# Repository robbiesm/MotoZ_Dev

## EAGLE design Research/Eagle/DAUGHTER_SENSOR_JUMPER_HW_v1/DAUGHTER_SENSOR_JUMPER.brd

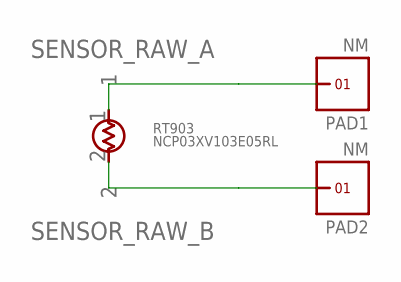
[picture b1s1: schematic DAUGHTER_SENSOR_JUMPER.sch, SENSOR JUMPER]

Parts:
PAD1, PAD2: NM; PAD_2X3
RT903: NCP03XV103E05RL; 0201

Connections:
SENSOR_RAW_A: PAD1.1, RT903.1
SENSOR_RAW_B: PAD2.1, RT903.2

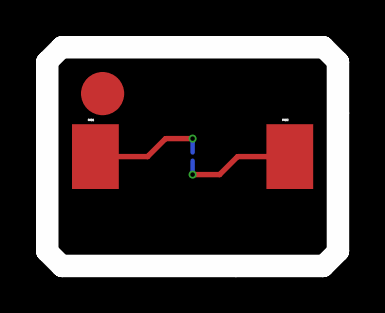
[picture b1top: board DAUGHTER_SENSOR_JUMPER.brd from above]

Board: 2 copper layers, 16.2 x 12.2 mm, 3 parts (1 on the bottom side), 2 nets.

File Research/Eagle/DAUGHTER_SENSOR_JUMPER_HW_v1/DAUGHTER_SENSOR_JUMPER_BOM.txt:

Partlist exported at 7/24/2016 6:41 PM

Qty Value           Device     Package Parts      Description                  MPN                                  SUPPLIER  
1   NCP03XV103E05RL THERMISTOR 0201    RT903      Thmistor, NTC 10Khm 3%, 0201 NCP03XV103XV103E05RL/NTCG0603UH103HT MURARA/TDK
2   NM              PUCK       PAD_2X3 PAD1, PAD2 test pad

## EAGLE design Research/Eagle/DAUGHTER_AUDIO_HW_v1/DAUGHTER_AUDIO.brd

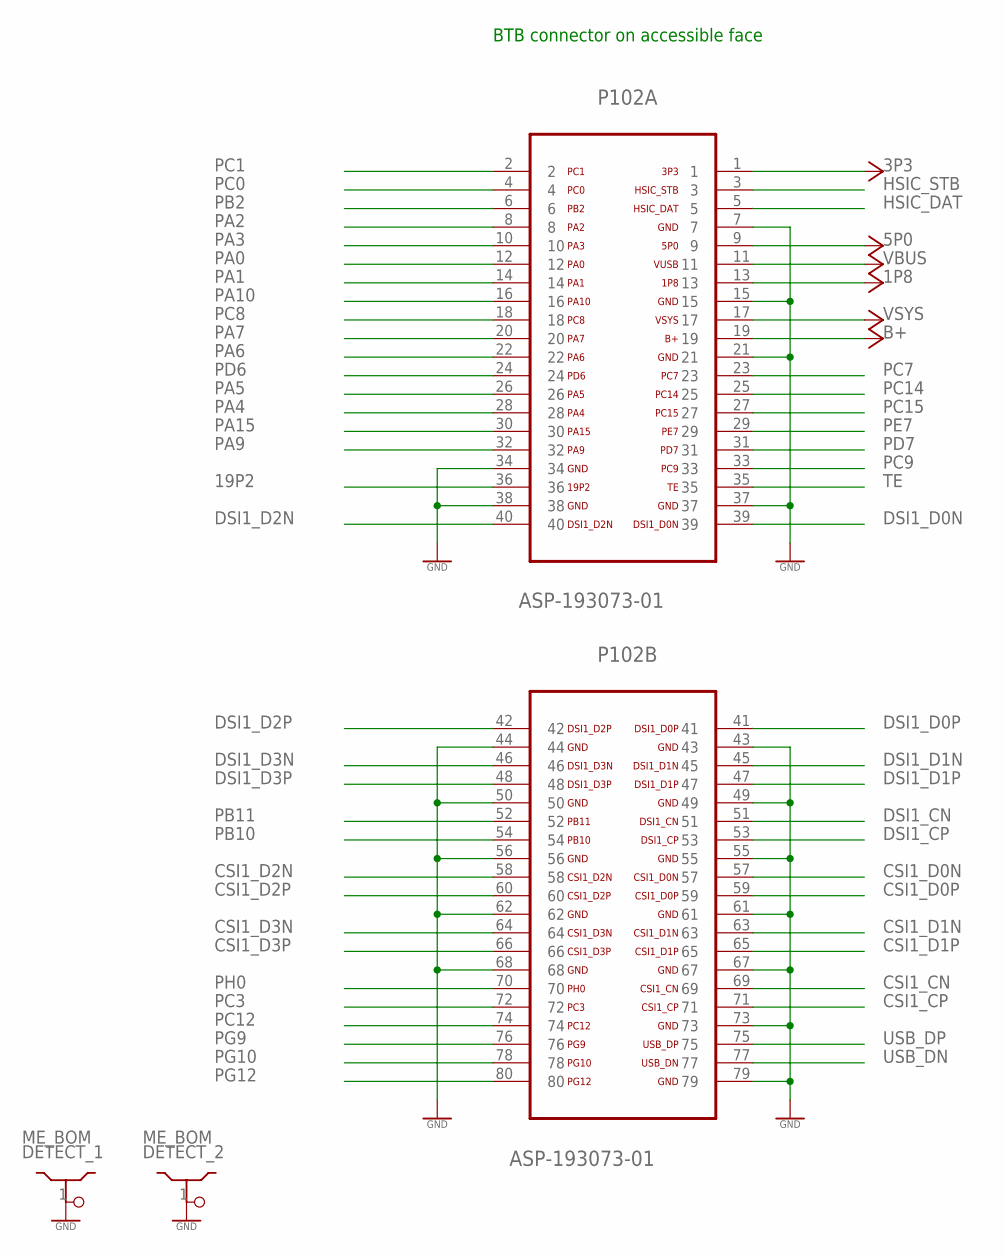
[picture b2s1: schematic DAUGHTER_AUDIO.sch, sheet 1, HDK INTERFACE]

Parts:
DETECT_1, DETECT_2: ME_BOM; PLUG
P102: ASP-193073-01; FTMH-140-02-L-DV-ES-P-TR; MPN ASP-193073-01

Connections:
1P8: P102.13; also elsewhere on the board
3P3: P102.1; also elsewhere on the board
5P0: P102.9
19P2: P102.36
B+: P102.19; also elsewhere on the board
CSI1_CN: P102.69
CSI1_CP: P102.71
CSI1_D0N: P102.57
CSI1_D0P: P102.59
CSI1_D1N: P102.63
CSI1_D1P: P102.65
CSI1_D2N: P102.58
CSI1_D2P: P102.60
CSI1_D3N: P102.64
CSI1_D3P: P102.66
DSI1_CN: P102.51
DSI1_CP: P102.53
DSI1_D0N: P102.39
DSI1_D0P: P102.41
DSI1_D1N: P102.45
DSI1_D1P: P102.47
DSI1_D2N: P102.40
DSI1_D2P: P102.42
DSI1_D3N: P102.46
DSI1_D3P: P102.48
GND: DETECT_1.1, DETECT_2.1, P102.7, P102.15, P102.21, P102.34, P102.37, P102.38, P102.43, P102.44, P102.49, P102.50, P102.55, P102.56, P102.61, P102.62, P102.67, P102.68, P102.73, P102.79; also elsewhere on the board
HSIC_DAT: P102.5
HSIC_STB: P102.3
PA0: P102.12
PA1: P102.14
PA2: P102.8
PA3: P102.10
PA4: P102.28
PA5: P102.26
PA6: P102.22
PA7: P102.20
PA9: P102.32
PA10: P102.16
PA15: P102.30
PB2: P102.6
PB10: P102.54; also elsewhere on the board
PB11: P102.52; also elsewhere on the board
PC0: P102.4; also elsewhere on the board
PC1: P102.2; also elsewhere on the board
PC3: P102.72
PC7: P102.23; also elsewhere on the board
PC8: P102.18
PC9: P102.33
PC12: P102.74
PC14: P102.25; also elsewhere on the board
PC15: P102.27; also elsewhere on the board
PD6: P102.24
PD7: P102.31; also elsewhere on the board
PE7: P102.29; also elsewhere on the board
PG9: P102.76; also elsewhere on the board
PG10: P102.78; also elsewhere on the board
PG12: P102.80
PH0: P102.70; also elsewhere on the board
TE: P102.35
USB_DN: P102.77
USB_DP: P102.75
VBUS: P102.11
VSYS: P102.17

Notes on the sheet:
BTB connector on accessible face

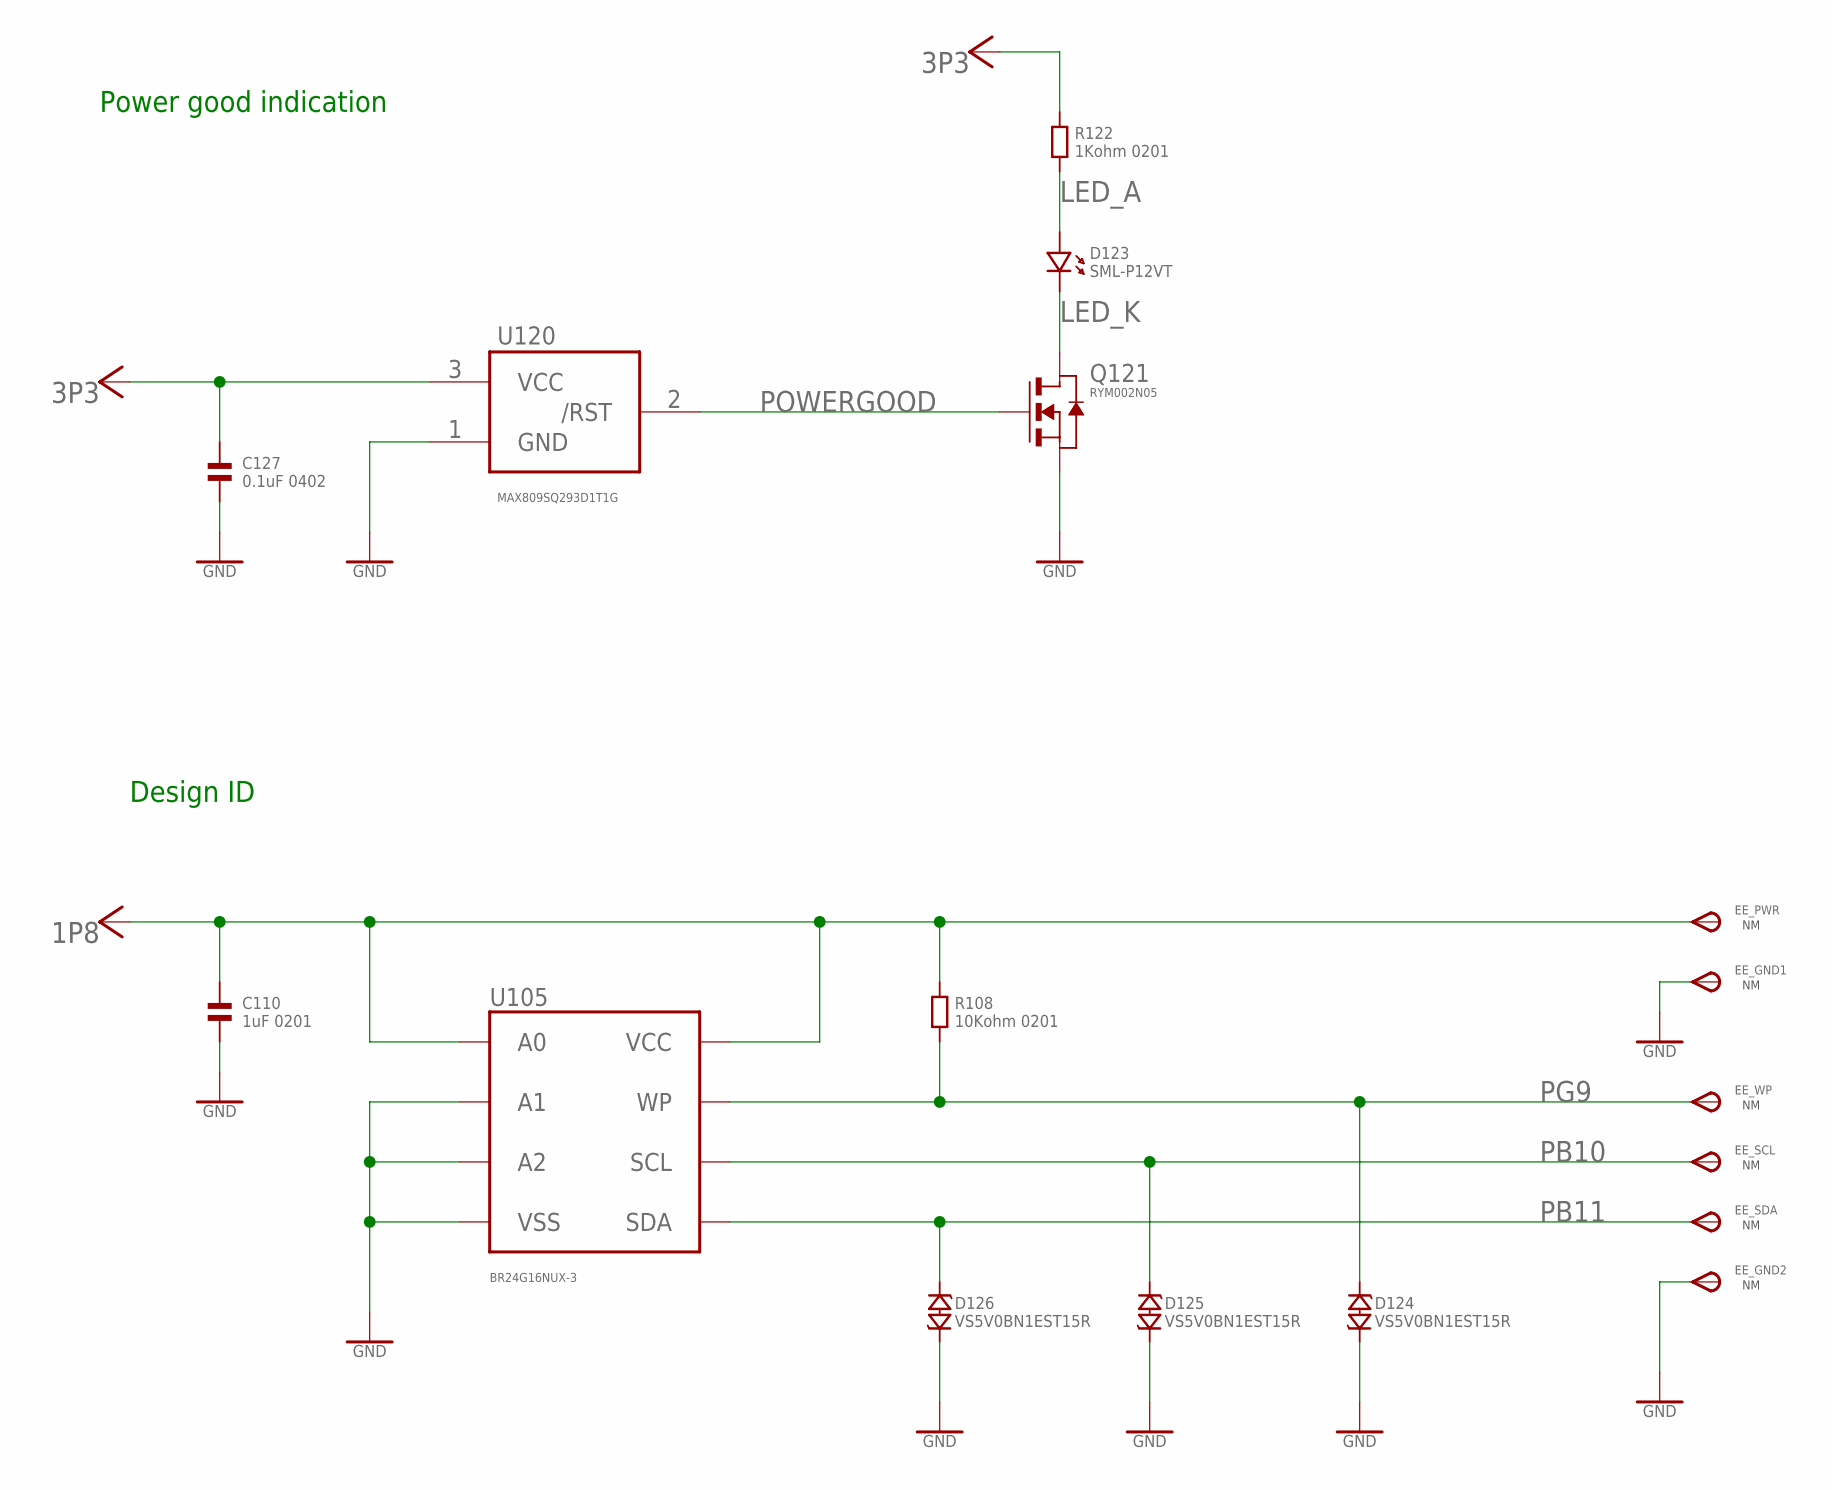
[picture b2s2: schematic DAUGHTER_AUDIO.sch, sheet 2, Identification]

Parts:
C110: 1uF 0201; 0201
C127: 0.1uF 0402; 0402
D123: SML-P12VT; 0503.LED
D124, D125, D126: VS5V0BN1EST15R; CHIP_0201
EE_GND1, EE_GND2: NM; TP11R
EE_PWR: NM; TP11R
EE_SCL: NM; TP11R
EE_SDA: NM; TP11R
EE_WP: NM; TP11R
Q121: RYM002N05; VMT3
R108: 10Kohm 0201; 0201
R122: 1Kohm 0201; 0201
U105: BR24G16NUX-3; DFN-8
U120: MAX809SQ293D1T1G; SC70-3L

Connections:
1P8: C110.1, EE_PWR.TP, R108.1, U105.P$1 (A0), U105.P$8 (VCC); also elsewhere on the board
3P3: C127.1, R122.1, U120.3 (VCC); also elsewhere on the board
GND: C110.2, C127.2, D124.P$2 (2), D125.P$2 (2), D126.P$2 (2), EE_GND1.TP, EE_GND2.TP, Q121.2 (S), U105.P$2 (A1), U105.P$3 (A2), U105.P$4 (VSS), U105.P$9 (VSS), U120.1 (GND); also elsewhere on the board
LED_A: D123.P$1 (1), R122.2
LED_K: D123.P$2 (2), Q121.3 (D)
PB10: D125.P$1 (1), EE_SCL.TP, U105.P$6 (SCL); also elsewhere on the board
PB11: D126.P$1 (1), EE_SDA.TP, U105.P$5 (SDA); also elsewhere on the board
PG9: D124.P$1 (1), EE_WP.TP, R108.2, U105.P$7 (WP); also elsewhere on the board
POWERGOOD: Q121.1 (G), U120.2 (/RST)

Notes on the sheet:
Power good indication
Design ID

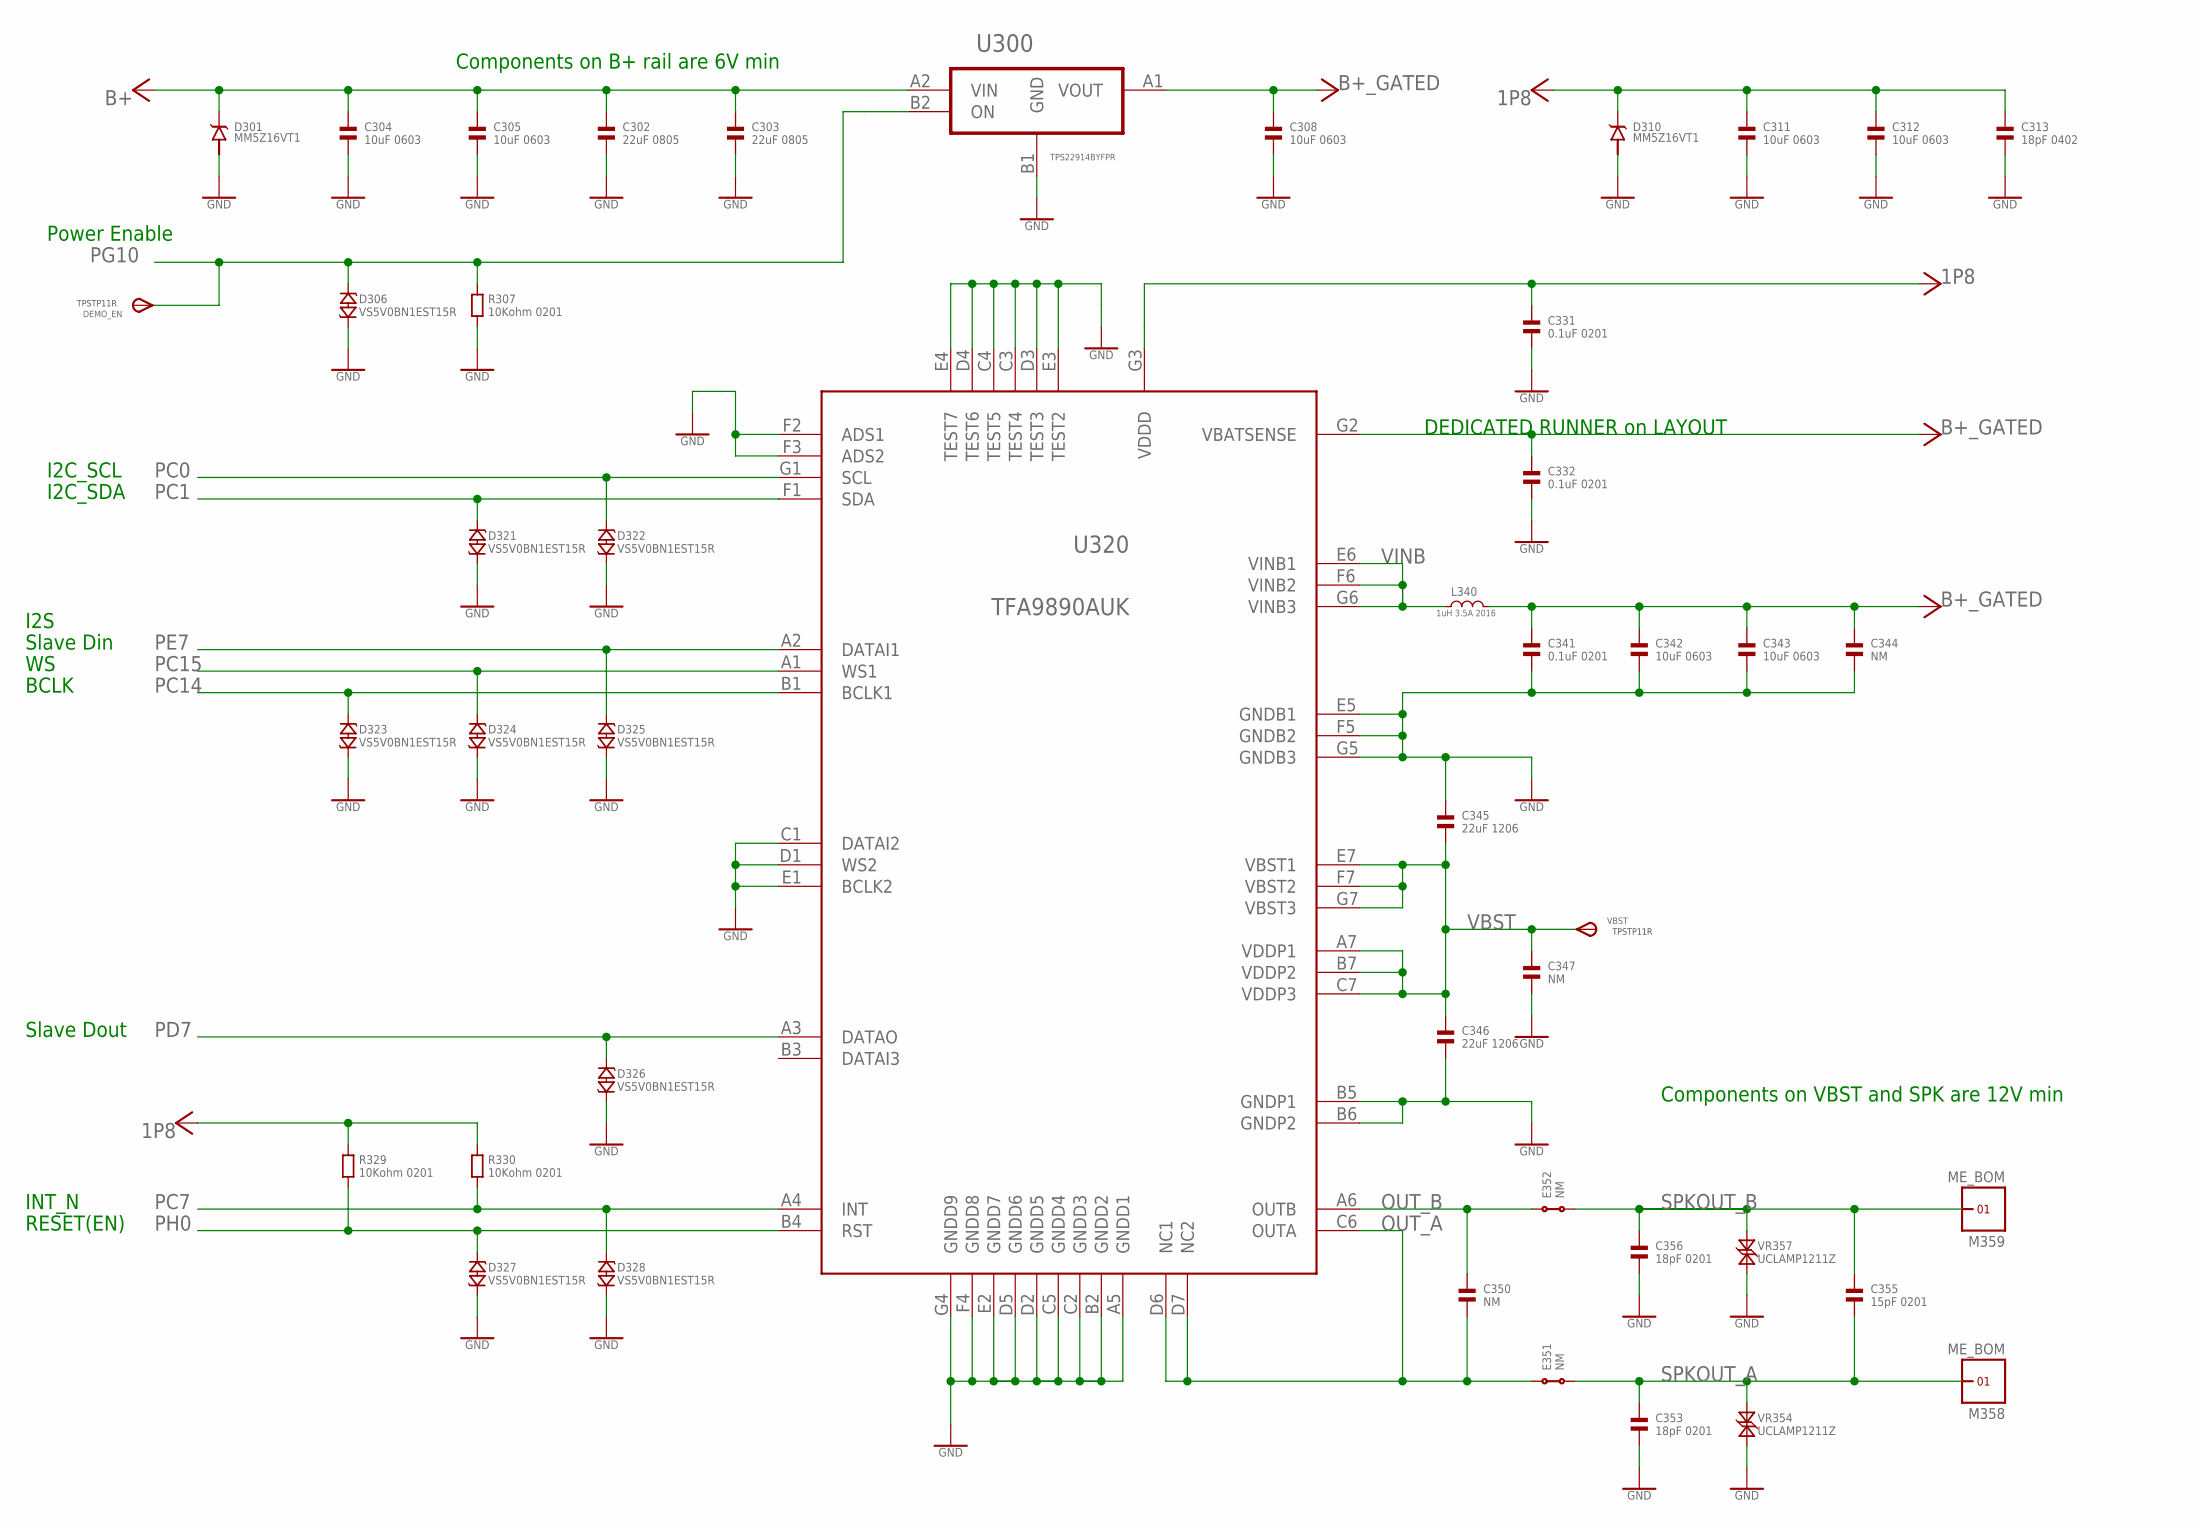
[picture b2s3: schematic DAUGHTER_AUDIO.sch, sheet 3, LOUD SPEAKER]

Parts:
C302, C303: 22uF 0805; 0805
C304, C305, C308, C311, C312, C342, C343: 10uF 0603; 0603
C313: 18pF 0402; 0402
C331, C332, C341: 0.1uF 0201; 0201
C344, C347: NM; 0402
C345, C346: 22uF 1206; 1206
C350: NM; 0201
C353, C356: 18pF 0201; 0201
C355: 15pF 0201; 0201
D301, D310: MM5Z16VT1; SOD523
D306, D321, D322, D323, D324, D325, D326, D327, D328: VS5V0BN1EST15R; CHIP_0201
DEMO_EN: TPSTP11R; TP11R
E351, E352: NM; 0603_SHORT
L340: 1uH 3.5A 2016; 2016
M358, M359: ME_BOM; PUCK
R307, R329, R330: 10Kohm 0201; 0201
U300: TPS22914BYFPR; BGA0_75SQ_PS0_4_P4
U320: TFA9890AUK; BGA7X7
VBST: TPSTP11R; TP11R
VR354, VR357: UCLAMP1211Z; CHIP_0201

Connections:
1P8: C311.1, C312.1, C313.1, C331.1, D310.1, R329.1, R330.1, U320.G3 (VDDD); also elsewhere on the board
B+: C302.1, C303.1, C304.1, C305.1, D301.1, U300.A2 (VIN); also elsewhere on the board
B+_GATED: C308.1, C332.1, C341.1, C342.1, C343.1, C344.1, L340.2, U300.A1 (VOUT), U320.G2 (VBATSENSE)
GND: C302.2, C303.2, C304.2, C305.2, C308.2, C311.2, C312.2, C313.2, C331.2, C332.2, C341.2, C342.2, C343.2, C344.2, C345.1, C346.2, C347.2, C353.2, C356.2, D301.2, D306.P$2 (2), D310.2, D321.P$2 (2), D322.P$2 (2), D323.P$2 (2), D324.P$2 (2), D325.P$2 (2), D326.P$2 (2), D327.P$2 (2), D328.P$2 (2), R307.2, U300.B1 (GND), U320.A5 (GNDD1), U320.B2 (GNDD2), U320.B5 (GNDP1), U320.B6 (GNDP2), U320.C1 (DATAI2), U320.C2 (GNDD3), U320.C3 (TEST4), U320.C4 (TEST5), U320.C5 (GNDD4), U320.D1 (WS2), U320.D2 (GNDD5), U320.D3 (TEST3), U320.D4 (TEST6), U320.D5 (GNDD6), U320.E1 (BCLK2), U320.E2 (GNDD7), U320.E3 (TEST2), U320.E4 (TEST7), U320.E5 (GNDB1), U320.F2 (ADS1), U320.F3 (ADS2), U320.F4 (GNDD8), U320.F5 (GNDB2), U320.G4 (GNDD9), U320.G5 (GNDB3), VR354.P$2 (2), VR357.P$2 (2); also elsewhere on the board
OUT_A: C350.2, E351.1, U320.C6 (OUTA), U320.D6 (NC1), U320.D7 (NC2)
OUT_B: C350.1, E352.1, U320.A6 (OUTB)
PC0: D322.P$1 (1), U320.G1 (SCL); also elsewhere on the board
PC1: D321.P$1 (1), U320.F1 (SDA); also elsewhere on the board
PC7: D328.P$1 (1), R330.2, U320.A4 (INT); also elsewhere on the board
PC14: D323.P$1 (1), U320.B1 (BCLK1); also elsewhere on the board
PC15: D324.P$1 (1), U320.A1 (WS1); also elsewhere on the board
PD7: D326.P$1 (1), U320.A3 (DATAO); also elsewhere on the board
PE7: D325.P$1 (1), U320.A2 (DATAI1); also elsewhere on the board
PG10: D306.P$1 (1), DEMO_EN.TP, R307.1, U300.B2 (ON); also elsewhere on the board
PH0: D327.P$1 (1), R329.2, U320.B4 (RST); also elsewhere on the board
SPKOUT_A: C353.1, C355.2, E351.2, M358.1, VR354.P$1 (1)
SPKOUT_B: C355.1, C356.1, E352.2, M359.1, VR357.P$1 (1)
VBST: C345.2, C346.1, C347.1, U320.A7 (VDDP1), U320.B7 (VDDP2), U320.C7 (VDDP3), U320.E7 (VBST1), U320.F7 (VBST2), U320.G7 (VBST3), VBST.TP
VINB: L340.1, U320.E6 (VINB1), U320.F6 (VINB2), U320.G6 (VINB3)

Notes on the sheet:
Power Enable
I2C_SCL
I2C_SDA
BCLK
I2S
Slave Dout
Slave Din
INT_N
RESET(EN)
DEDICATED RUNNER on LAYOUT
Components on VBST and SPK are 12V min
Components on B+ rail are 6V min

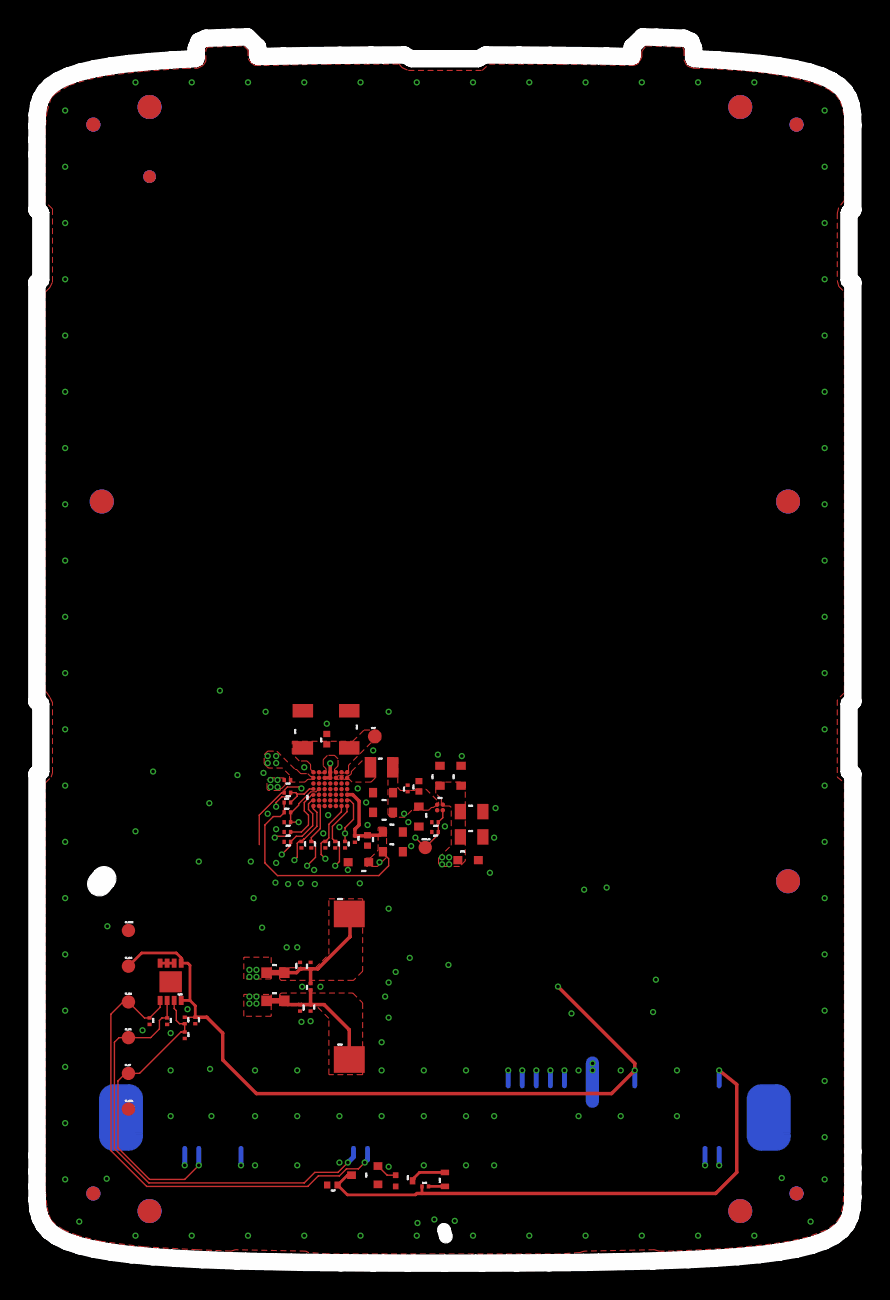
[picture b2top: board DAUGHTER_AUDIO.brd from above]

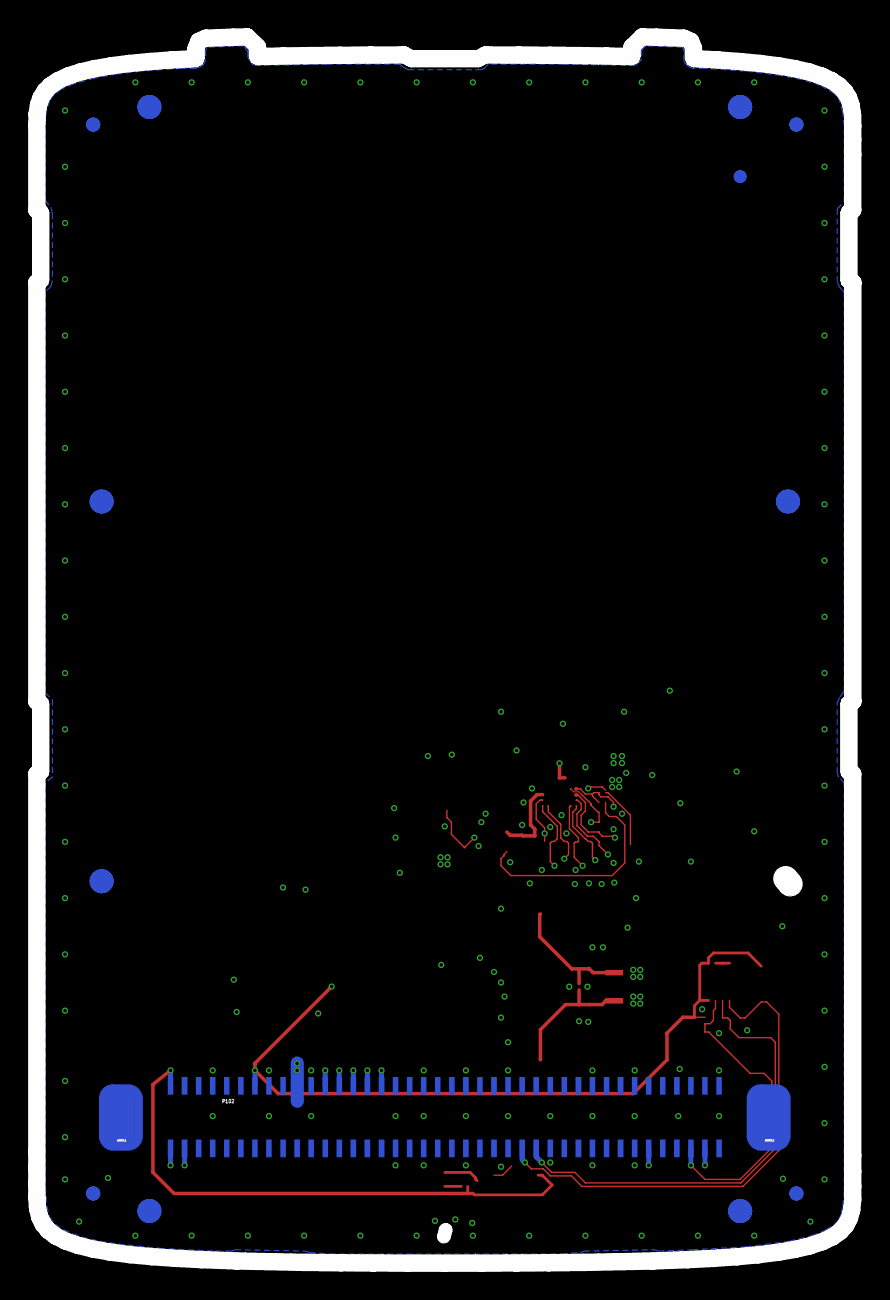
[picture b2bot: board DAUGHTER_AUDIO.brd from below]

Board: 4 copper layers, 58.1 x 87.2 mm, 66 parts (3 on the bottom side), 26 nets.

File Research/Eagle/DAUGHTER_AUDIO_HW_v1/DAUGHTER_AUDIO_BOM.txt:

Partlist exported at 7/24/2016 6:28 PM

Qty Value            Device                   Package                  Parts                                                                  Description                             MPN             SUPPLIER       
3   0.1uF 0201       CAPACITOR.0201           0201                     C331, C332, C341                                                       Ceramic Capacitor, Generic                                             
1   0.1uF 0402       CAPACITOR.0402           0402                     C127                                                                   Ceramic Capacitor, Generic                                             
4   10Kohm 0201      RESISTOR.0201            0201                     R108, R307, R329, R330                                                 Resistor - Generic                                                     
7   10uF 0603        CAPACITOR.0603           0603                     C304, C305, C308, C311, C312, C342, C343                               Ceramic Capacitor, Generic                                             
1   15pF 0201        CAPACITOR.0201           0201                     C355                                                                   Ceramic Capacitor, Generic                                             
2   18pF 0201        CAPACITOR.0201           0201                     C353, C356                                                             Ceramic Capacitor, Generic                                             
1   18pF 0402        CAPACITOR.0402           0402                     C313                                                                   Ceramic Capacitor, Generic                                             
1   1Kohm 0201       RESISTOR.0201            0201                     R122                                                                   Resistor - Generic                                                     
1   1uF 0201         CAPACITOR.0201           0201                     C110                                                                   Ceramic Capacitor, Generic                                             
1   1uH 3.5A 2016    POWER-INDUCTOR.2016      2016                     L340                                                                   Inductor, Power                                                        
2   22uF 0805        CAPACITOR.0805           0805                     C302, C303                                                             Ceramic Capacitor, Generic                                             
2   22uF 1206        CAPACITOR.1206           1206                     C345, C346                                                             Ceramic Capacitor, Generic                                             
1   ASP-193073-01    FTMH-140-02-L-DV-ES-P-TR FTMH-140-02-L-DV-ES-P-TR P102                                                                   MICRO SOCKET, 1.0MM, SMD, 2X40WAY, MALE ASP-193073-01   SAMTEC         
1   BR24G16NUX-3     EEPROMDFN8               DFN-8                    U105                                                                   I2C EE PROM, 8 pin                      BR24G16NUX-3    ROHM           
1   MAX809SQ293D1T1G MAX809                   SC70-3L                  U120                                                                   3-Pin Microprocessor Reset Circuit      MAX809SQ293D1T1 ON-SEMI        
2   ME_BOM           PUCK.PUCK                PUCK                     M358, M359                                                             test pad                                refer to ME BOM refer to ME BOM
2   ME_BOM           SHIELDDETECT             PLUG                     DETECT_1, DETECT_2                                                     Shield, Custom                          refer to ME BOM ref to ME BOM  
2   MM5Z16VT1        DIODE.SOD523             SOD523                   D301, D310                                                             DIODE GENERIC, single, 2 pin            MM5Z16VT1       ON_SEMI        
1   NM               CAPACITOR.0201           0201                     C350                                                                   Ceramic Capacitor, Generic                                             
2   NM               CAPACITOR.0402           0402                     C344, C347                                                             Ceramic Capacitor, Generic                                             
2   NM               SHORT_BAR.0603           0603_SHORT               E351, E352                                                             SHORT BAR - layout feature                                             
6   NM               TPSTP11R                 TP11R                    EE_GND1, EE_GND2, EE_PWR, EE_SCL, EE_SDA, EE_WP                        TEST Point, 1mm diameter, gold                                         
1   RYM002N05        FET-NRYM002N05           VMT3                     Q121                                                                   Generic NMOS FET                        RYM002N05       ROHM           
1   SML-P12VT        LED.0503                 0503.LED                 D123                                                                   LED GENERIC, single, 2 pin              SML-P12VT       ROHM           
1   TFA9890AUK       TFA9890AUK               BGA7X7                   U320                                                                   Audio Power amplifier                   TFA9890AUK      NXP            
1   TPS22914BYFPR    TPS22914BYFPR            BGA0_75SQ_PS0_4_P4       U300                                                                   5V load switch                          TPS22914BYFPR   TI             
2   TPSTP11R         TPSTP11R                 TP11R                    DEMO_EN, VBST                                                          TEST Point, 1mm diameter, gold                                         
2   UCLAMP1211Z      ESD_TVS.0201             CHIP_0201                VR354, VR357                                                           GENERIC TVS,single, 2 pin               UCLAMP1211Z     SEMTECH        
12  VS5V0BN1EST15R   ESD_VARISTOR.0201        CHIP_0201                D124, D125, D126, D306, D321, D322, D323, D324, D325, D326, D327, D328 GENERIC varistor,single, 2 pin          VS5V0BN1EST15R  ROHM

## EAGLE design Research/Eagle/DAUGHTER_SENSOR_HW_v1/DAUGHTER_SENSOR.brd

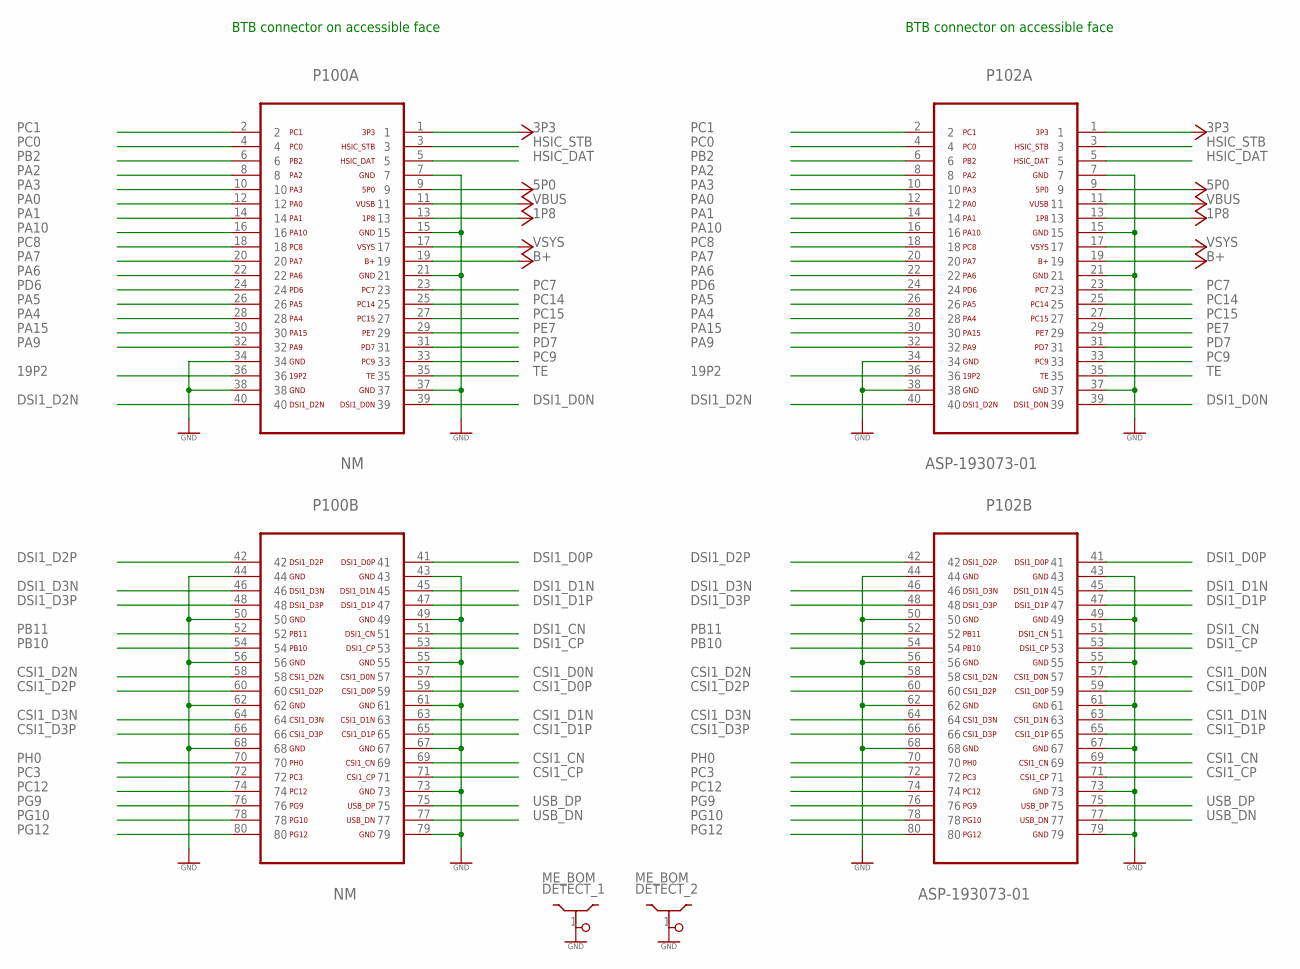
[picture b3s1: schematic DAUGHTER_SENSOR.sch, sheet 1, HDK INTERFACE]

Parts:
DETECT_1, DETECT_2: ME_BOM; PLUG
P100: NM; CLM-140-02-L-D-K_GOLD
P102: ASP-193073-01; FTMH-140-02-L-DV-ES-P-TR; MPN ASP-193073-01

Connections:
1P8: P100.13, P102.13; also elsewhere on the board
3P3: P100.1, P102.1; also elsewhere on the board
5P0: P100.9, P102.9
19P2: P100.36, P102.36
B+: P100.19, P102.19
CSI1_CN: P100.69, P102.69
CSI1_CP: P100.71, P102.71
CSI1_D0N: P100.57, P102.57
CSI1_D0P: P100.59, P102.59
CSI1_D1N: P100.63, P102.63
CSI1_D1P: P100.65, P102.65
CSI1_D2N: P100.58, P102.58
CSI1_D2P: P100.60, P102.60
CSI1_D3N: P100.64, P102.64
CSI1_D3P: P100.66, P102.66
DSI1_CN: P100.51, P102.51
DSI1_CP: P100.53, P102.53
DSI1_D0N: P100.39, P102.39
DSI1_D0P: P100.41, P102.41
DSI1_D1N: P100.45, P102.45
DSI1_D1P: P100.47, P102.47
DSI1_D2N: P100.40, P102.40
DSI1_D2P: P100.42, P102.42
DSI1_D3N: P100.46, P102.46
DSI1_D3P: P100.48, P102.48
GND: DETECT_1.1, DETECT_2.1, P100.7, P100.15, P100.21, P100.34, P100.37, P100.38, P100.43, P100.44, P100.49, P100.50, P100.55, P100.56, P100.61, P100.62, P100.67, P100.68, P100.73, P100.79, P102.7, P102.15, P102.21, P102.34, P102.37, P102.38, P102.43, P102.44, P102.49, P102.50, P102.55, P102.56, P102.61, P102.62, P102.67, P102.68, P102.73, P102.79; also elsewhere on the board
HSIC_DAT: P100.5, P102.5
HSIC_STB: P100.3, P102.3
PA0: P100.12, P102.12
PA1: P100.14, P102.14
PA2: P100.8, P102.8
PA3: P100.10, P102.10
PA4: P100.28, P102.28
PA5: P100.26, P102.26
PA6: P100.22, P102.22
PA7: P100.20, P102.20
PA9: P100.32, P102.32
PA10: P100.16, P102.16
PA15: P100.30, P102.30
PB2: P100.6, P102.6
PB10: P100.54, P102.54; also elsewhere on the board
PB11: P100.52, P102.52; also elsewhere on the board
PC0: P100.4, P102.4; also elsewhere on the board
PC1: P100.2, P102.2; also elsewhere on the board
PC3: P100.72, P102.72; also elsewhere on the board
PC7: P100.23, P102.23
PC8: P100.18, P102.18
PC9: P100.33, P102.33
PC12: P100.74, P102.74
PC14: P100.25, P102.25
PC15: P100.27, P102.27
PD6: P100.24, P102.24
PD7: P100.31, P102.31
PE7: P100.29, P102.29
PG9: P100.76, P102.76; also elsewhere on the board
PG10: P100.78, P102.78; also elsewhere on the board
PG12: P100.80, P102.80
PH0: P100.70, P102.70
TE: P100.35, P102.35
USB_DN: P100.77, P102.77
USB_DP: P100.75, P102.75
VBUS: P100.11, P102.11
VSYS: P100.17, P102.17

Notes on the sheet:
BTB connector on accessible face
